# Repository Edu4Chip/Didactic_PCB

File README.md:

# Didactic PCB
This repository includes design files and documentation for Didactic PCBs and software for the power management microcontroller on the PCB.

## Folders
Doc: All documentation is gathered within this folder.
PCBs: KiCad projects Didactic main and wire bond PCBs.
PM_MCU_software: STM32CubeIDE project for the power management microcontroller on the PCB.

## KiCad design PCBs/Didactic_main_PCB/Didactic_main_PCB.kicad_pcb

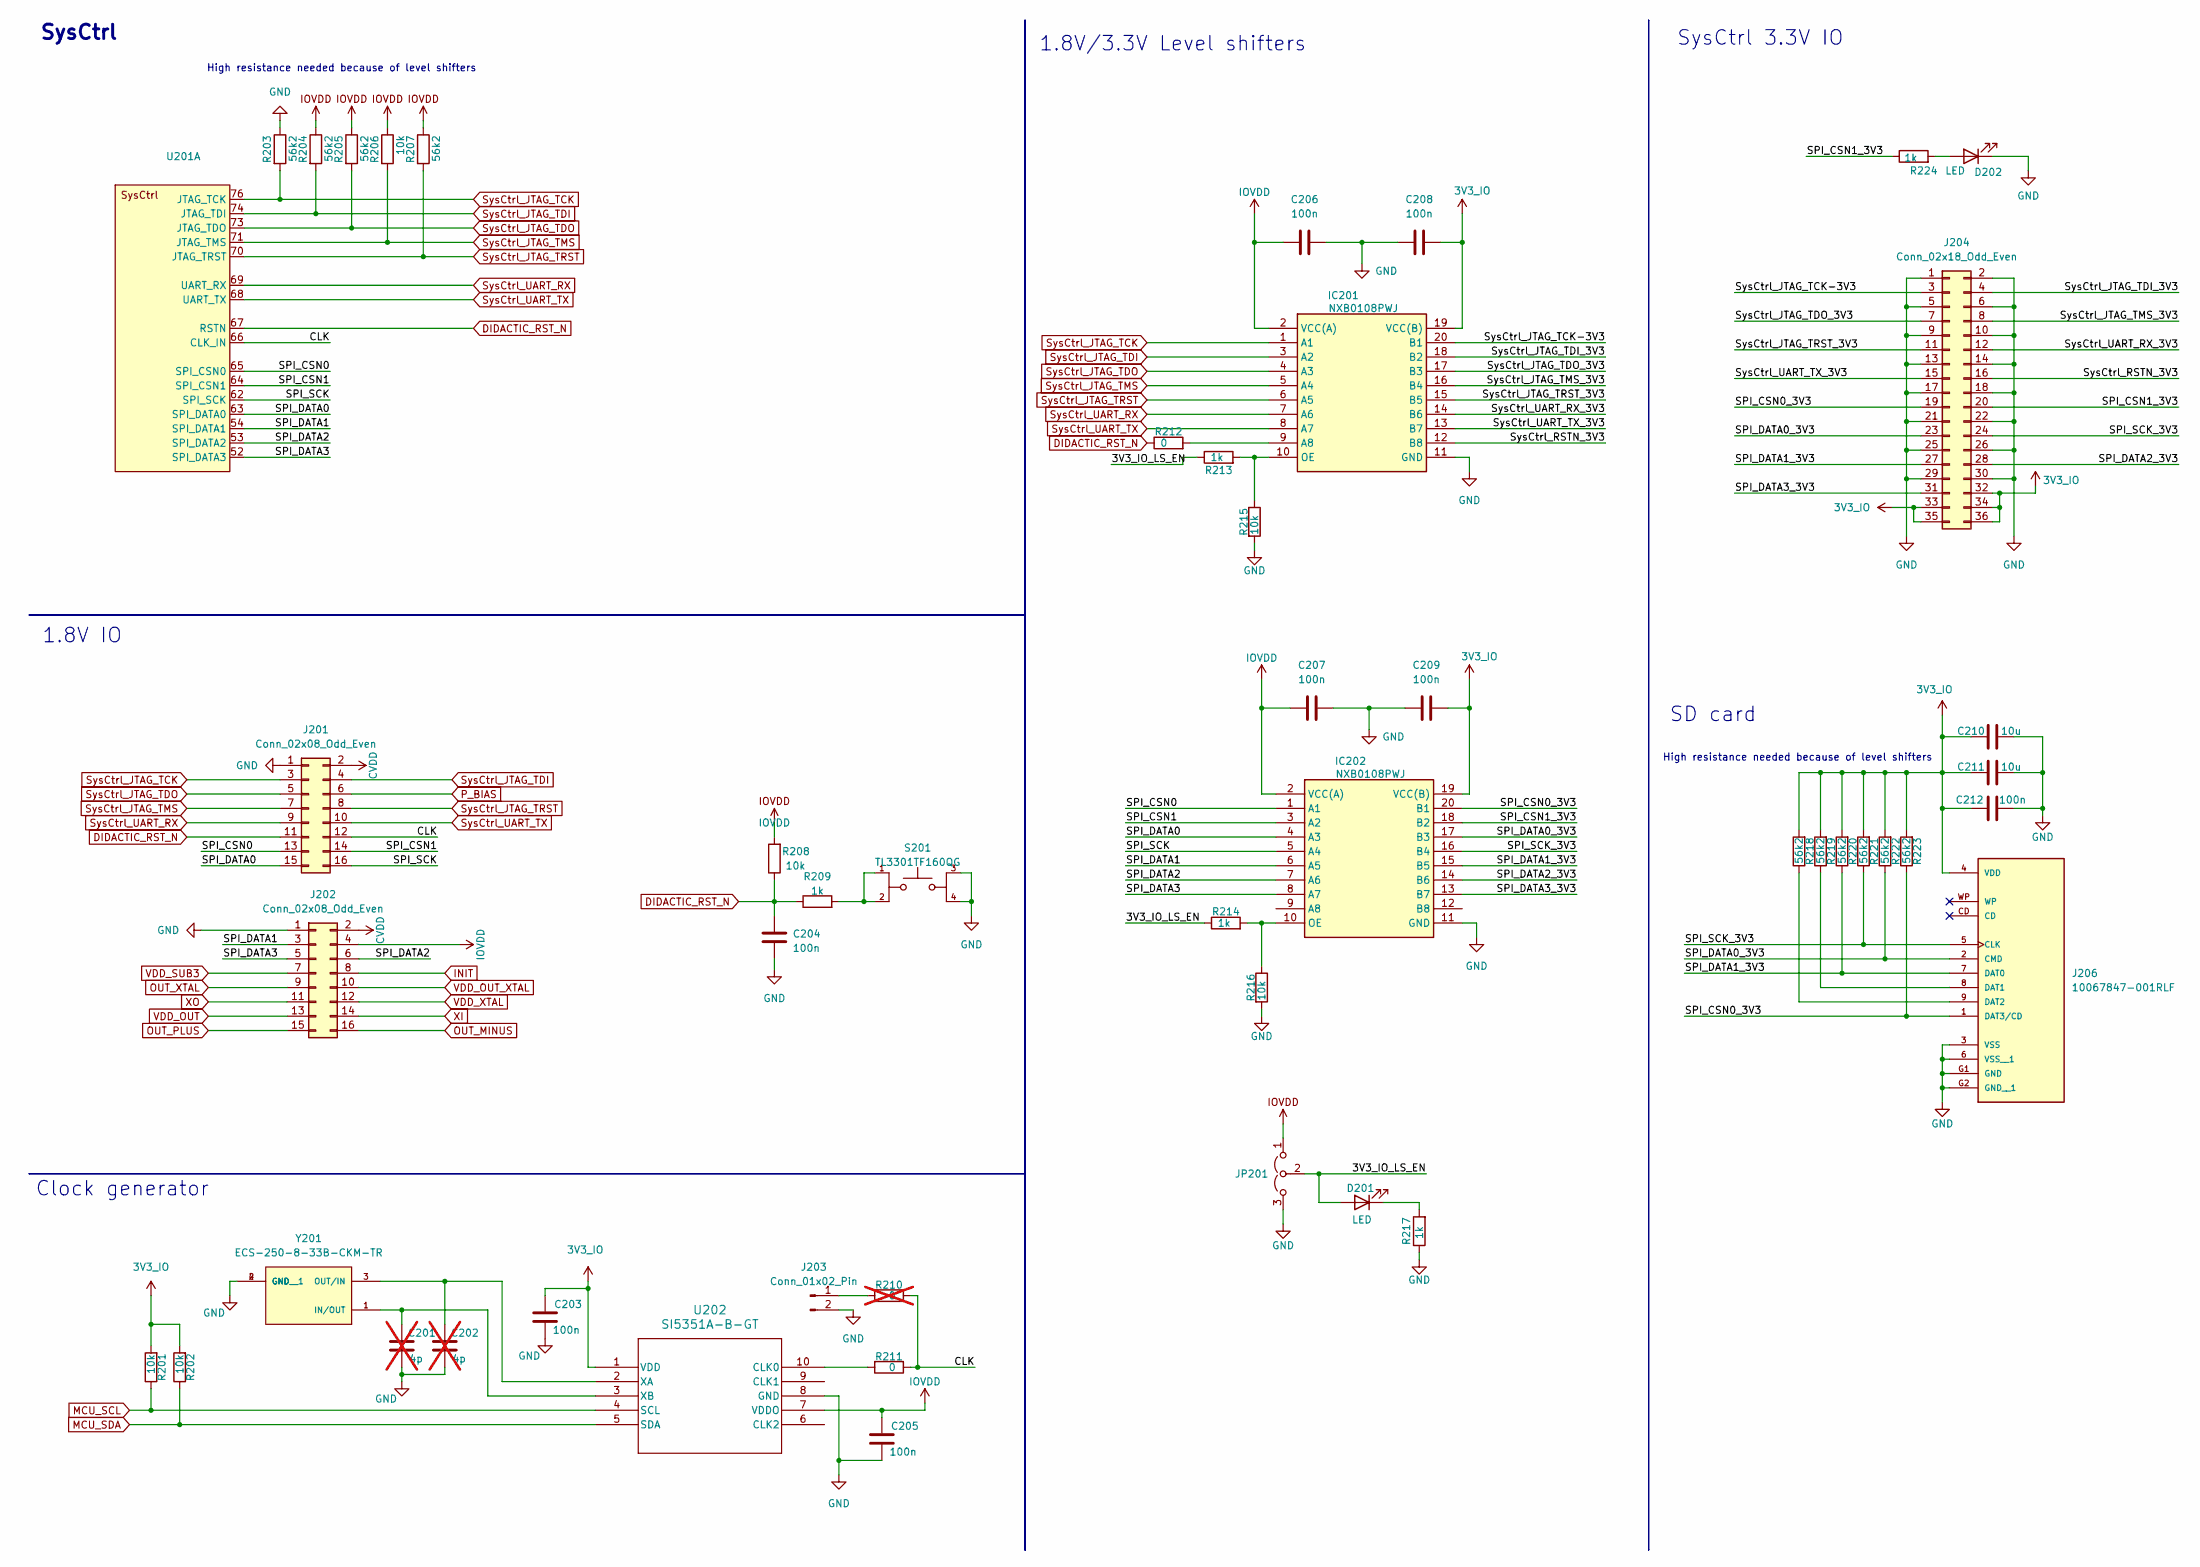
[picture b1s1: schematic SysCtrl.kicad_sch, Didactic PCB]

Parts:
C201, C202: 4p; C_0603_1608Metric; not fitted
C203, C204, C205, C206, C207, C208, C209, C212: 100n; C_0603_1608Metric; MANUFACTURER_PART_NUMBER GPC0603104
C210, C211: 10u; C_0805_2012Metric; MANUFACTURER_PART_NUMBER GPC0805106-25
D201, D202: LED; LED_0603_1608Metric; MANUFACTURER_PART_NUMBER APHD1608LSURCK
IC201, IC202: NXB0108PWJ; Mouser Part Number 771-NXB0108PWJ
J201, J202: Conn_02x08_Odd_Even; PinHeader_2x08_P2.54mm_Vertical; MANUFACTURER_PART_NUMBER 77313-101-16LF
J203: Conn_01x02_Pin; PinHeader_1x02_P2.54mm_Vertical; MANUFACTURER_PART_NUMBER 61300211121
J204: Conn_02x18_Odd_Even; PinHeader_2x18_P2.54mm_Vertical; MOUSER_PART_NUMBER 77313-101-36LF
J206: 10067847-001RLF; AMPHENOL_10067847-001RLF; PARTREV K
JP201: Jumper_3_Open; PinHeader_1x03_P2.54mm_Vertical; MANUFACTURER_PART_NUMBER 61300311121
R201, R202, R206, R208, R215, R216: 10k; R_0603_1608Metric; MANUFACTURER_PART_NUMBER GPR060310K
R203, R204, R205, R207, R218, R219, R220, R221, R222, R223: 56k2; R_0603_1608Metric; MANUFACTURER_PART_NUMBER CPF0603F56K2C1
R209, R213, R214, R217, R224: 1k; R_0603_1608Metric; MANUFACTURER_PART_NUMBER GPR06031K
R210: 0; R_0603_1608Metric; MANUFACTURER_PART_NUMBER GPR06030R; not fitted
R211, R212: 0; R_0603_1608Metric; MANUFACTURER_PART_NUMBER GPR06030R
S201: TL3301TF160QG; SW_TL3301TF160QG; PARTREV E
U201: Didactic_QFN-80_EP_12x12_Pitch0.5mm
U202: SI5351A-B-GT; MSOP10_SI5351_3X3-0P5_SKY; MANUFACTURER_PART_NUMBER SI5351A-B-GT
Y201: ECS-250-8-33B-CKM-TR; XTAL_ECS-250-8-33B-CKM-TR; MANUFACTURER_PART_NUMBER ECS-250-8-33B-CKM-TR

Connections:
3V3_IO: C203.2, C208.2, C209.2, C210.1, C211.1, C212.1, IC201.19 (VCC(B)), IC202.19 (VCC(B)), J204.32, J204.33, J204.34, J204.35, J204.36, J206.4 (VDD), R201.2, R202.2, R218.2, R219.2, R220.2, R221.2, R222.2, R223.2, U202.1 (VDD); also elsewhere on the board
/SysCtrl/3V3_IO_LS_EN: D201.2 (A), JP201.2 (C), R213.1, R214.1
/SysCtrl/CLK: J201.12, R210.1, R211.1, U201.66 (CLK_IN)
/SysCtrl/SPI_CSN0: IC202.1 (A1), J201.13, U201.65 (SPI_CSN0)
/SysCtrl/SPI_CSN0_3V3: IC202.20 (B1), J204.19, J206.1 (DAT3/CD), R223.1
/SysCtrl/SPI_CSN1: IC202.3 (A2), J201.14, U201.64 (SPI_CSN1)
/SysCtrl/SPI_CSN1_3V3: IC202.18 (B2), J204.20, R224.1
/SysCtrl/SPI_DATA0: IC202.4 (A3), J201.15, U201.63 (SPI_DATA0)
/SysCtrl/SPI_DATA0_3V3: IC202.17 (B3), J204.23, J206.2 (CMD), R222.1
/SysCtrl/SPI_DATA1: IC202.6 (A5), J202.3, U201.54 (SPI_DATA1)
/SysCtrl/SPI_DATA1_3V3: IC202.15 (B5), J204.27, J206.7 (DAT0), R220.1
/SysCtrl/SPI_DATA2: IC202.7 (A6), J202.6, U201.53 (SPI_DATA2)
/SysCtrl/SPI_DATA2_3V3: IC202.14 (B6), J204.28
/SysCtrl/SPI_DATA3: IC202.8 (A7), J202.5, U201.52 (SPI_DATA3)
/SysCtrl/SPI_DATA3_3V3: IC202.13 (B7), J204.31
/SysCtrl/SPI_SCK: IC202.5 (A4), J201.16, U201.62 (SPI_SCK)
/SysCtrl/SPI_SCK_3V3: IC202.16 (B4), J204.24, J206.5 (CLK), R221.1
/SysCtrl/SysCtrl_JTAG_TCK-3V3: IC201.20 (B1), J204.3
/SysCtrl/SysCtrl_JTAG_TDI_3V3: IC201.18 (B2), J204.4
/SysCtrl/SysCtrl_JTAG_TDO_3V3: IC201.17 (B3), J204.7
/SysCtrl/SysCtrl_JTAG_TMS_3V3: IC201.16 (B4), J204.8
/SysCtrl/SysCtrl_JTAG_TRST_3V3: IC201.15 (B5), J204.11
/SysCtrl/SysCtrl_RSTN_3V3: IC201.12 (B8), J204.16
/SysCtrl/SysCtrl_UART_RX_3V3: IC201.14 (B6), J204.12
/SysCtrl/SysCtrl_UART_TX_3V3: IC201.13 (B7), J204.15
CVDD: J201.2, J202.2; also elsewhere on the board
DIDACTIC_RST_N: C204.1, J201.11, R208.1, R209.1, R212.1, U201.67 (RSTN); also elsewhere on the board
GND: C201.1, C202.1, C203.1, C204.2, C205.1, C206.2, C207.2, C208.1, C209.1, C210.2, C211.2, C212.2, D202.1 (K), IC201.11 (GND), IC202.11 (GND), J201.1, J202.1, J203.2, J204.1, J204.2, J204.5, J204.6, J204.9, J204.10, J204.13, J204.14, J204.17, J204.18, J204.21, J204.22, J204.25, J204.26, J204.29, J204.30, J206.3 (VSS), J206.6 (VSS__1), J206.G1 (GND), J206.G2 (GND__1), JP201.3 (B), R203.1, R215.2, R216.2, R217.1, S201.3, S201.4, U202.8 (GND), Y201.2 (GND), Y201.4 (GND__1); also elsewhere on the board
INIT: J202.8; also elsewhere on the board
IOVDD: C205.2, C206.1, C207.1, IC201.2 (VCC(A)), IC202.2 (VCC(A)), J202.4, JP201.1 (A), R204.1, R205.1, R206.1, R207.1, R208.2, U202.7 (VDDO); also elsewhere on the board
MCU_SCL: R201.1, U202.4 (SCL); also elsewhere on the board
MCU_SDA: R202.1, U202.5 (SDA); also elsewhere on the board
unnamed: D201.1 (K), R217.2
unnamed: D202.2 (A), R224.2
unnamed: IC201.9 (A8), R212.2
unnamed: IC201.10 (OE), R213.2, R215.1
unnamed: IC202.10 (OE), R214.2, R216.1
unnamed: J203.1, R210.2
unnamed: J206.8 (DAT1), R219.1
unnamed: J206.9 (DAT2), R218.1
unnamed: R209.2, S201.1, S201.2
unnamed: R211.2, U202.10 (CLK0)
unnamed: C202.2, U202.2 (XA), Y201.3 (OUT/IN)
unnamed: C201.2, U202.3 (XB), Y201.1 (IN/OUT)
OUT_MINUS: J202.16; also elsewhere on the board
OUT_PLUS: J202.15; also elsewhere on the board
OUT_XTAL: J202.9; also elsewhere on the board
P_BIAS: J201.6; also elsewhere on the board
SysCtrl_JTAG_TCK: IC201.1 (A1), J201.3, R203.2, U201.76 (JTAG_TCK); also elsewhere on the board
SysCtrl_JTAG_TDI: IC201.3 (A2), J201.4, R204.2, U201.74 (JTAG_TDI); also elsewhere on the board
SysCtrl_JTAG_TDO: IC201.4 (A3), J201.5, R205.2, U201.73 (JTAG_TDO); also elsewhere on the board
SysCtrl_JTAG_TMS: IC201.5 (A4), J201.7, R206.2, U201.71 (JTAG_TMS); also elsewhere on the board
SysCtrl_JTAG_TRST: IC201.6 (A5), J201.8, R207.2, U201.70 (JTAG_TRST)
SysCtrl_UART_RX: IC201.7 (A6), J201.9, U201.69 (UART_RX); also elsewhere on the board
SysCtrl_UART_TX: IC201.8 (A7), J201.10, U201.68 (UART_TX); also elsewhere on the board
VDD_OUT: J202.13; also elsewhere on the board
VDD_OUT_XTAL: J202.10; also elsewhere on the board
VDD_SUB3: J202.7; also elsewhere on the board
VDD_XTAL: J202.12; also elsewhere on the board
XI: J202.14; also elsewhere on the board
XO: J202.11; also elsewhere on the board

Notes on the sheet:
SysCtrl 3.3V IO
1.8V/3.3V Level shifters
SD card
High resistance needed because of level shifters
SysCtrl
Clock generator
1.8V IO

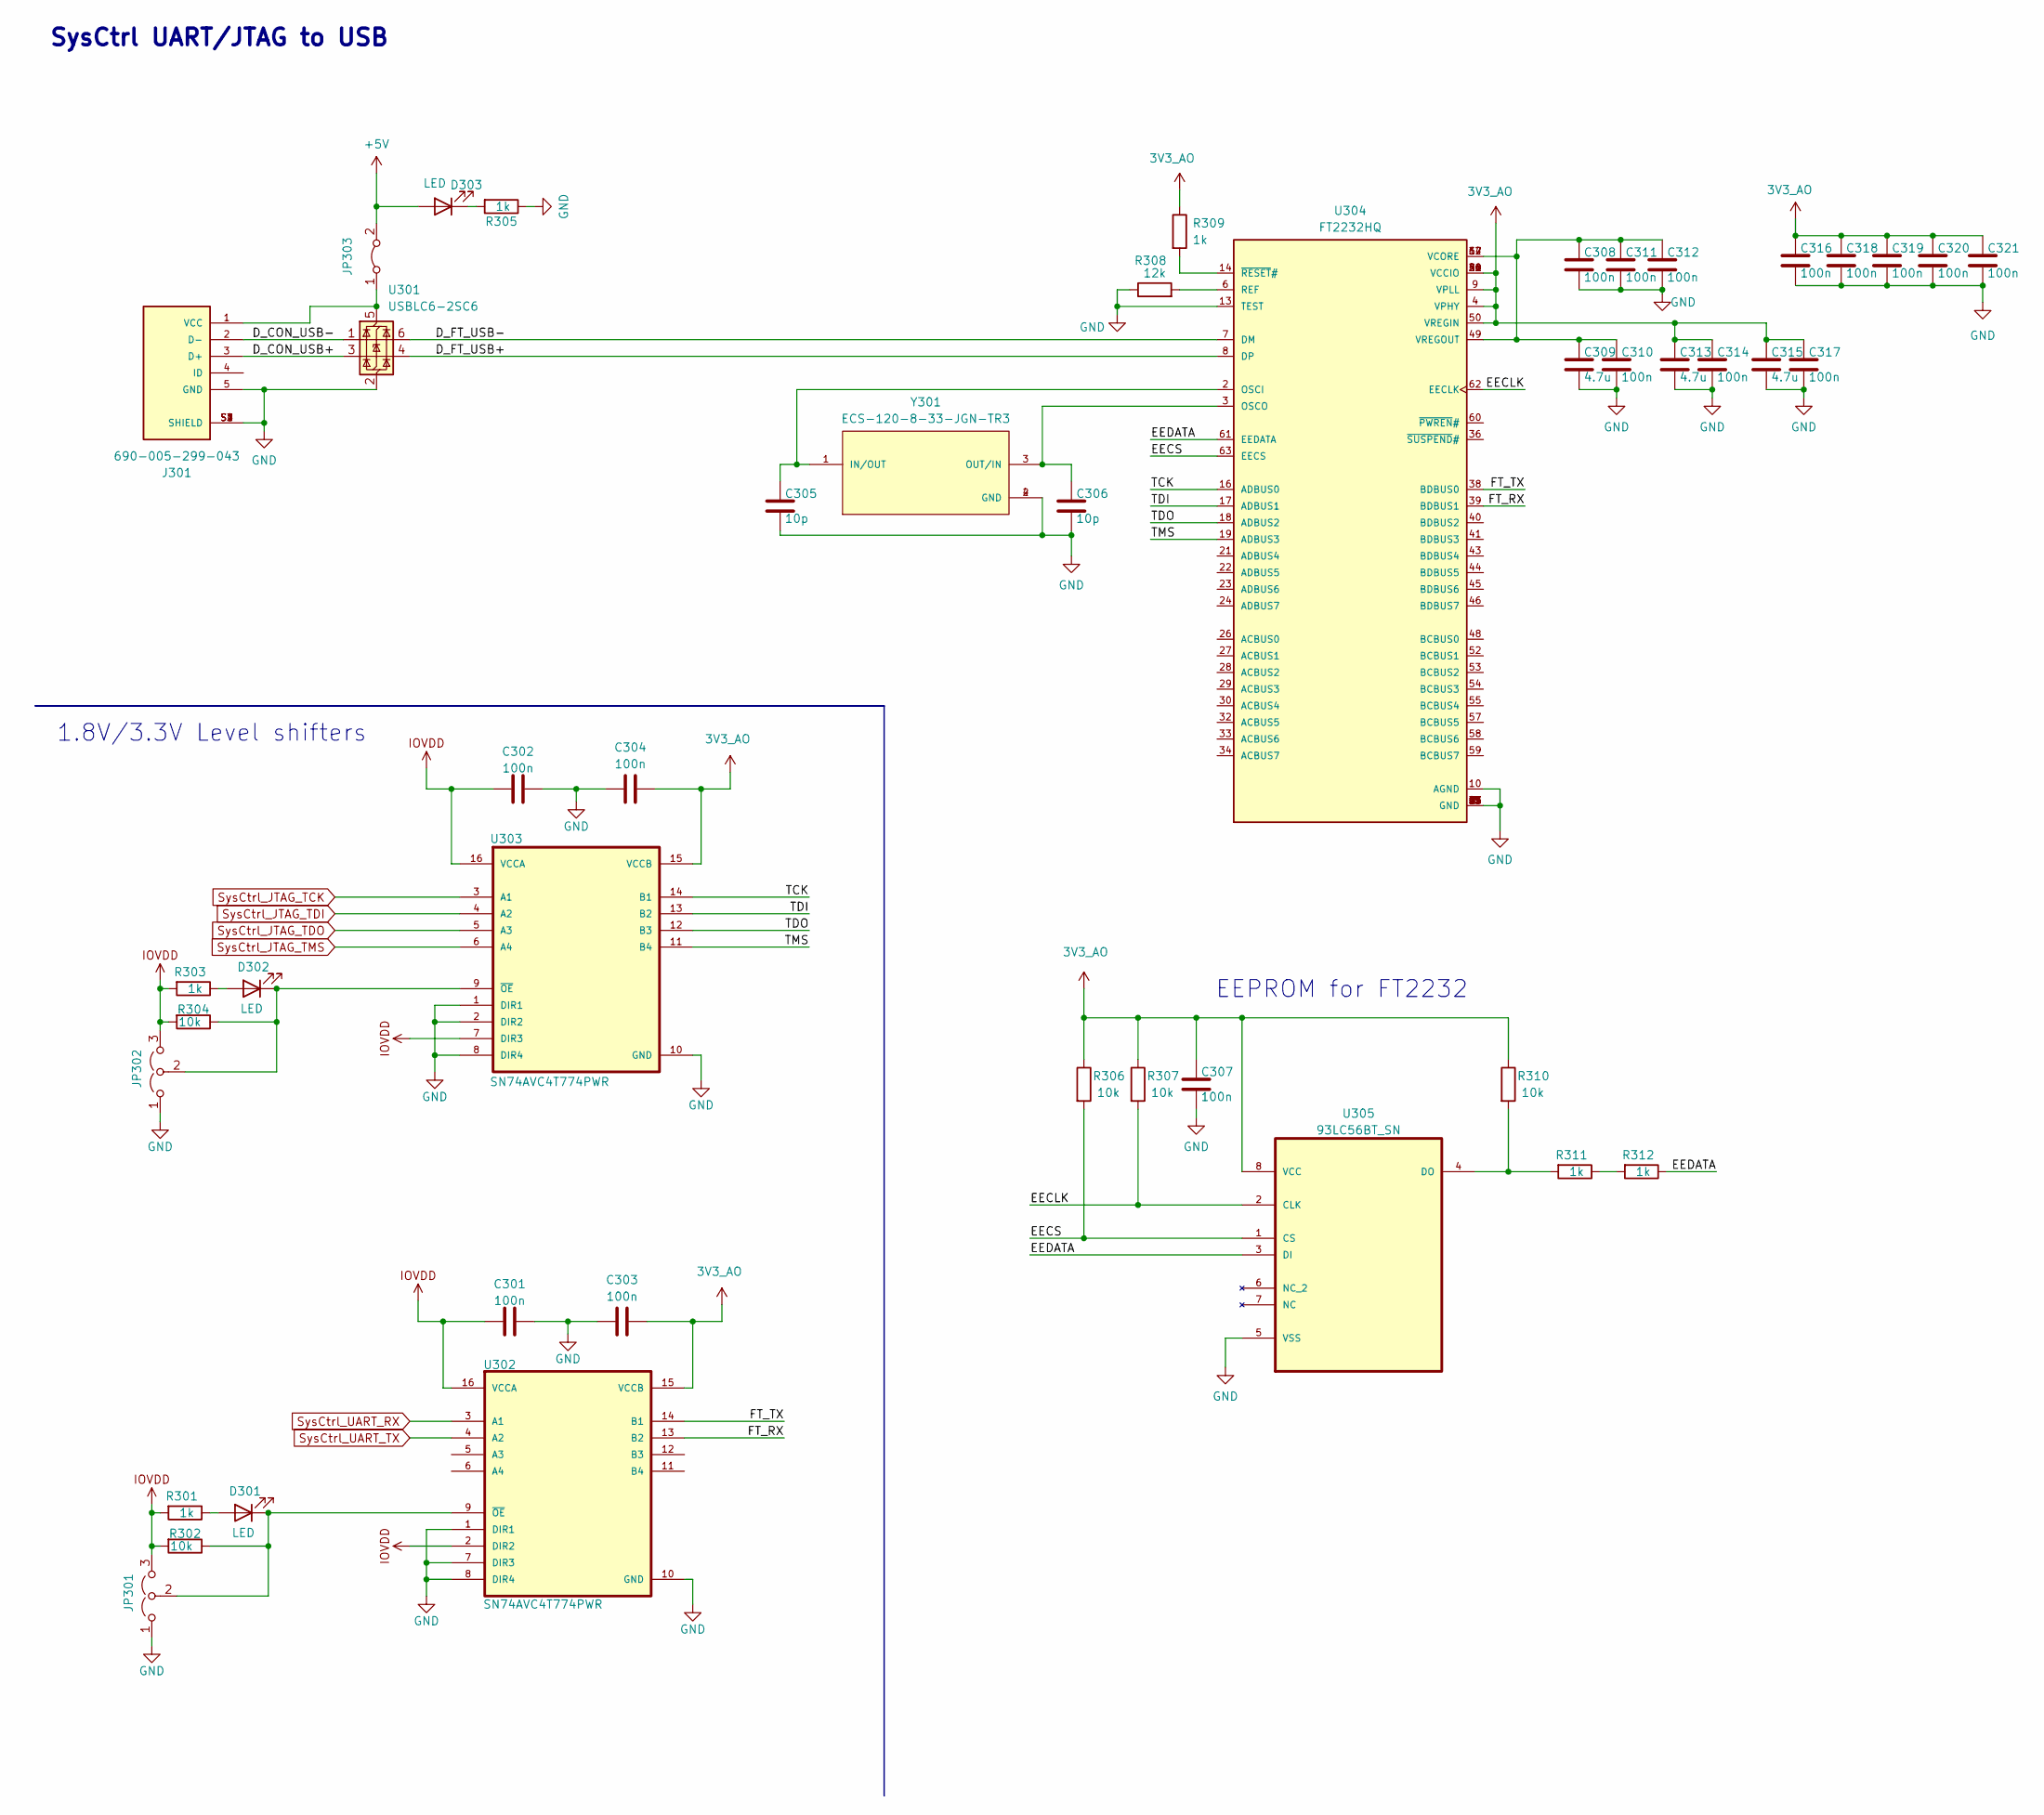
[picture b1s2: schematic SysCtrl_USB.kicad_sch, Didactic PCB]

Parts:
C301, C302, C303, C304, C307, C308, C310, C311, C312, C314, C316, C317, C318, C319, C320, C321: 100n; C_0603_1608Metric; MANUFACTURER_PART_NUMBER GPC0603104
C305, C306: 10p; C_0603_1608Metric; MANUFACTURER_PART_NUMBER GPC0603100
C309, C313, C315: 4.7u; C_0603_1608Metric; MANUFACTURER_PART_NUMBER GPC0603475-10
D301, D302, D303: LED; LED_0603_1608Metric; MANUFACTURER_PART_NUMBER APHD1608LSURCK
J301: 690-005-299-043; EDAC_690-005-299-043; PARTREV 11
JP301, JP302: Jumper_3_Open; PinHeader_1x03_P2.54mm_Vertical; MANUFACTURER_PART_NUMBER 61300311121
JP303: Jumper_2_Bridged; PinHeader_1x02_P2.54mm_Vertical; MANUFACTURER_PART_NUMBER 61300211121
R301, R303, R305, R309, R311, R312: 1k; R_0603_1608Metric; MANUFACTURER_PART_NUMBER GPR06031K
R302, R304, R306, R307, R310: 10k; R_0603_1608Metric; MANUFACTURER_PART_NUMBER GPR060310K
R308: 12k; R_0603_1608Metric; MANUFACTURER_PART_NUMBER GPR060312K
U301: USBLC6-2SC6; SOT-23-6; MANUFACTURER_PART_NUMBER USBLC6-2SC6
U302, U303: SN74AVC4T774PWR; SOP65P640X120-16N; MANUFACTURER_PART_NUMBER SN74AVC4T774PWR
U304: FT2232HQ; QFN50P900X900X100-65N; MANUFACTURER_PART_NUMBER FT2232HQ
U305: 93LC56BT_SN; SOIC127P600X175-8N; MPN 93LC56BT/SN
Y301: ECS-120-8-33-JGN-TR3; XTAL_ECS-120-8-33-JGN-TR3; MANUFACTURER_PART_NUMBER ECS-120-8-33-JGN-TR3

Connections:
3V3_AO: C303.2, C304.2, C307.1, C313.1, C314.1, C315.1, C316.1, C317.1, C318.1, C319.1, C320.1, C321.1, R306.1, R307.1, R309.1, R310.1, U302.15 (VCCB), U303.15 (VCCB), U304.4 (VPHY), U304.9 (VPLL), U304.20 (VCCIO), U304.31 (VCCIO), U304.42 (VCCIO), U304.50 (VREGIN), U304.56 (VCCIO), U305.8 (VCC); also elsewhere on the board
+5V: D303.2 (A), JP303.2 (B); also elsewhere on the board
/SysCtrl_USB/D_CON_USB+: J301.3 (D+), U301.3 (I/O2)
/SysCtrl_USB/D_CON_USB-: J301.2 (D-), U301.1 (I/O1)
/SysCtrl_USB/D_FT_USB+: U301.4 (I/O2), U304.8 (DP)
/SysCtrl_USB/D_FT_USB-: U301.6 (I/O1), U304.7 (DM)
/SysCtrl_USB/EECLK: R307.2, U304.62 (EECLK), U305.2 (CLK)
/SysCtrl_USB/EECS: R306.2, U304.63 (EECS), U305.1 (CS)
/SysCtrl_USB/EEDATA: R312.1, U304.61 (EEDATA), U305.3 (DI)
/SysCtrl_USB/FT_RX: U302.13 (B2), U304.39 (BDBUS1)
/SysCtrl_USB/FT_TX: U302.14 (B1), U304.38 (BDBUS0)
/SysCtrl_USB/TCK: U303.14 (B1), U304.16 (ADBUS0)
/SysCtrl_USB/TDI: U303.13 (B2), U304.17 (ADBUS1)
/SysCtrl_USB/TDO: U303.12 (B3), U304.18 (ADBUS2)
/SysCtrl_USB/TMS: U303.11 (B4), U304.19 (ADBUS3)
GND: C301.2, C302.2, C303.1, C304.1, C305.2, C306.2, C307.2, C308.2, C309.2, C310.2, C311.2, C312.2, C313.2, C314.2, C315.2, C316.2, C317.2, C318.2, C319.2, C320.2, C321.2, J301.5 (GND), J301.S1 (SHIELD), J301.S2 (SHIELD), J301.S3 (SHIELD), J301.S4 (SHIELD), JP301.1 (A), JP302.1 (A), R305.1, R308.1, U301.2 (GND), U302.1 (DIR1), U302.7 (DIR3), U302.8 (DIR4), U302.10 (GND), U303.1 (DIR1), U303.2 (DIR2), U303.8 (DIR4), U303.10 (GND), U304.1 (GND), U304.5 (GND), U304.10 (AGND), U304.11 (GND), U304.13 (TEST), U304.15 (GND), U304.25 (GND), U304.35 (GND), U304.47 (GND), U304.51 (GND), U304.65 (GND), U305.5 (VSS), Y301.2 (GND), Y301.4 (GND); also elsewhere on the board
IOVDD: C301.1, C302.1, JP301.3 (B), JP302.3 (B), R301.2, R302.2, R303.2, R304.2, U302.2 (DIR2), U302.16 (VCCA), U303.7 (DIR3), U303.16 (VCCA); also elsewhere on the board
unnamed: D301.2 (A), R301.1
unnamed: D301.1 (K), JP301.2 (C), R302.1, U302.9 (~OE)
unnamed: D302.2 (A), R303.1
unnamed: D302.1 (K), JP302.2 (C), R304.1, U303.9 (~OE)
unnamed: D303.1 (K), R305.2
unnamed: J301.1 (VCC), JP303.1 (A), U301.5 (VBUS)
unnamed: R311.1, R312.2
unnamed: C305.1, U304.2 (OSCI), Y301.1 (IN/OUT)
unnamed: C306.1, U304.3 (OSCO), Y301.3 (OUT/IN)
unnamed: R308.2, U304.6 (REF)
unnamed: C308.1, C309.1, C310.1, C311.1, C312.1, U304.12 (VCORE), U304.37 (VCORE), U304.49 (VREGOUT), U304.64 (VCORE)
unnamed: R309.2, U304.14 (~RESET#)
unnamed: R310.2, R311.2, U305.4 (DO)
SysCtrl_JTAG_TCK: U303.3 (A1); also elsewhere on the board
SysCtrl_JTAG_TDI: U303.4 (A2); also elsewhere on the board
SysCtrl_JTAG_TDO: U303.5 (A3); also elsewhere on the board
SysCtrl_JTAG_TMS: U303.6 (A4); also elsewhere on the board
SysCtrl_UART_RX: U302.3 (A1); also elsewhere on the board
SysCtrl_UART_TX: U302.4 (A2); also elsewhere on the board

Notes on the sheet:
SysCtrl UART/JTAG to USB
1.8V/3.3V Level shifters
EEPROM for FT2232

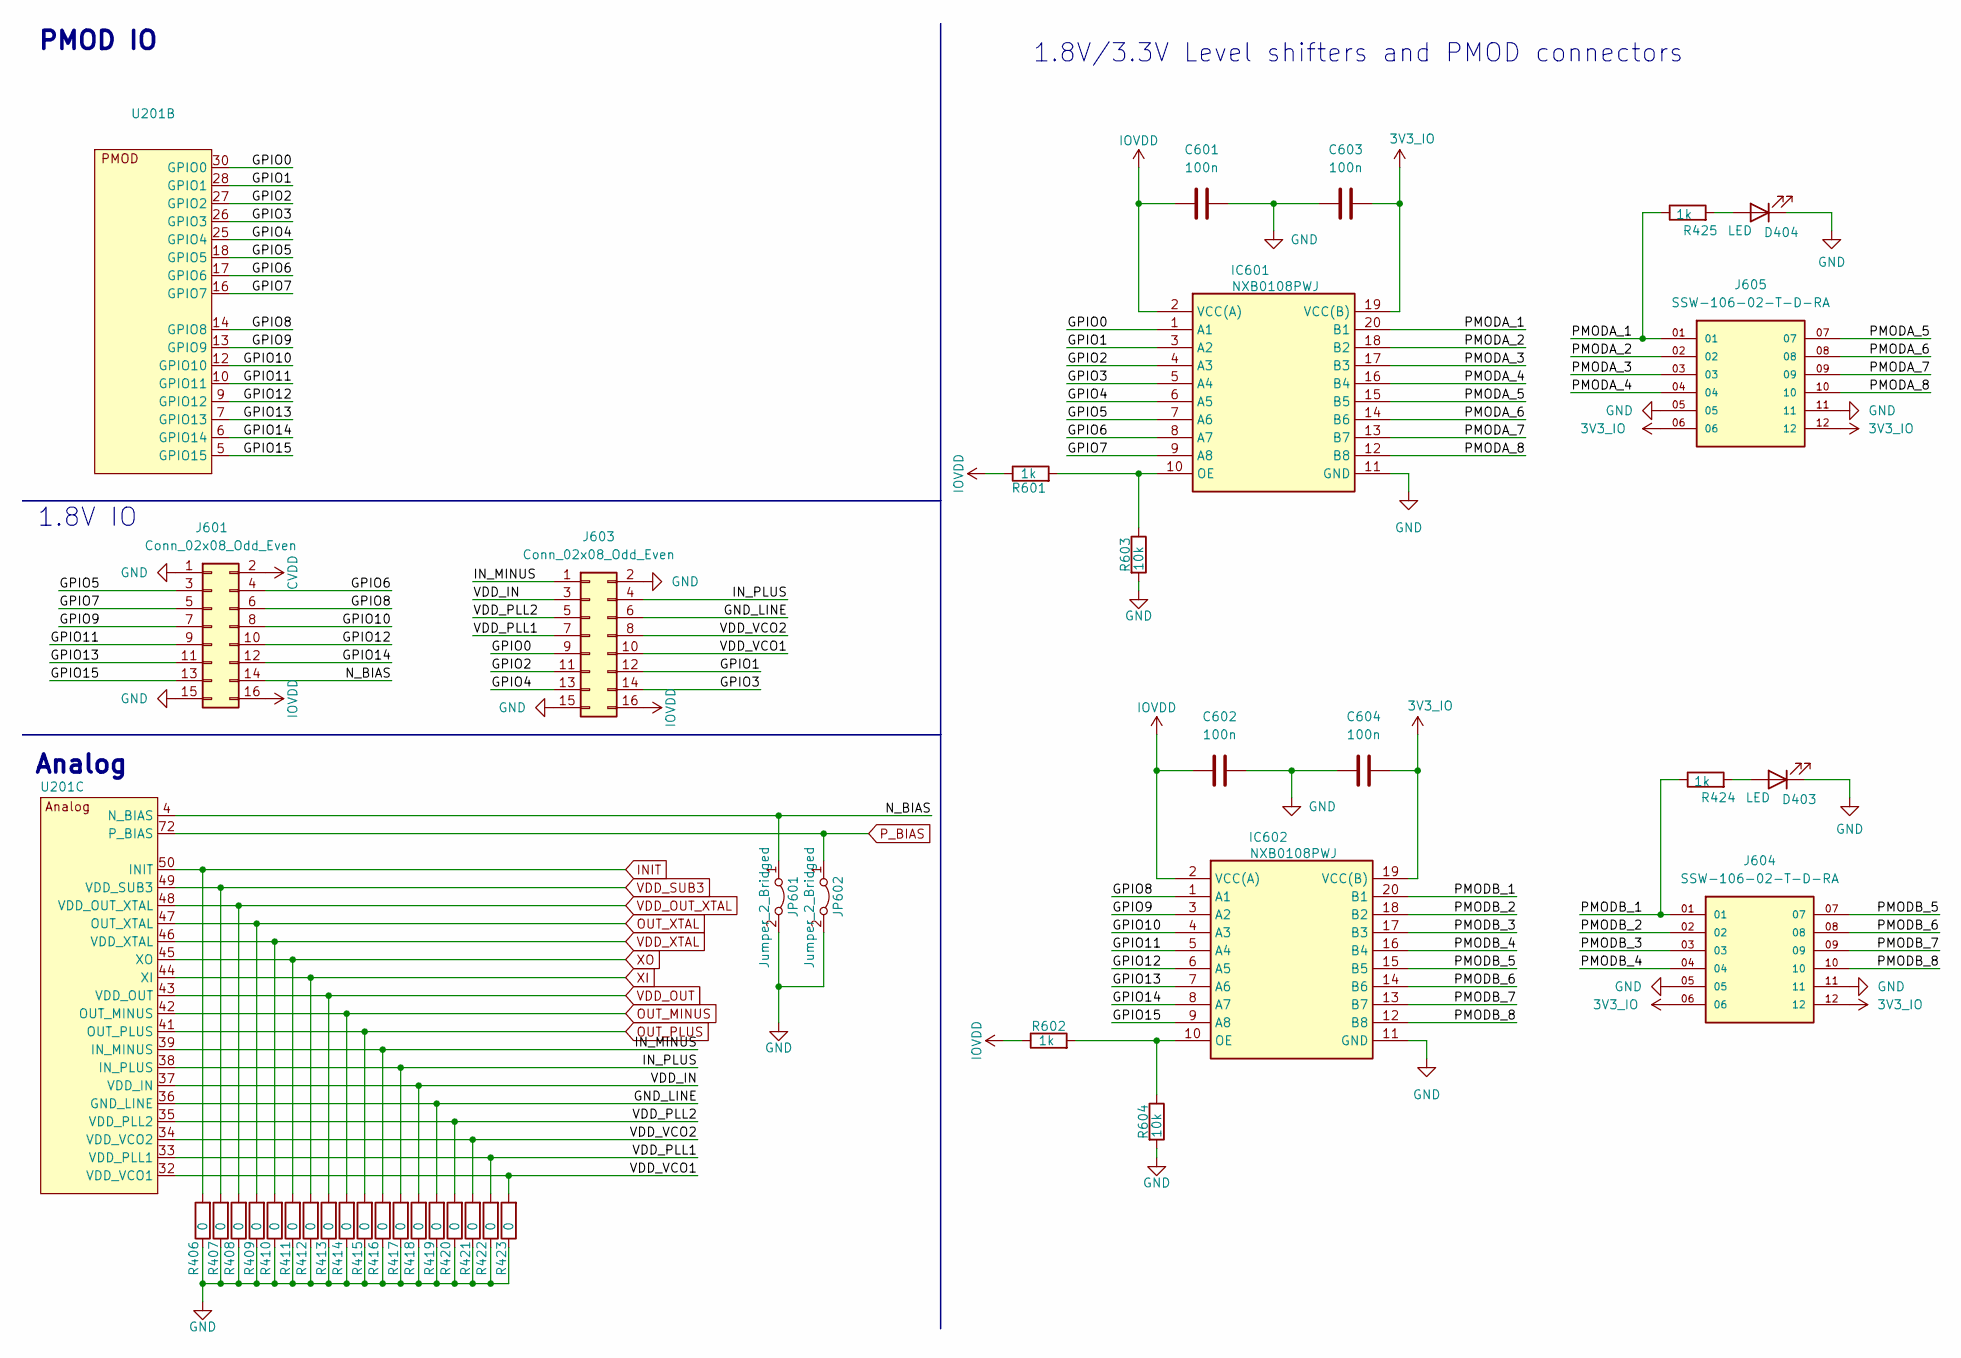
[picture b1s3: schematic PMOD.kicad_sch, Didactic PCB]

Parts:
C601, C602, C603, C604: 100n; C_0603_1608Metric; MANUFACTURER_PART_NUMBER GPC0603104
D403, D404: LED; LED_0603_1608Metric; MANUFACTURER_PART_NUMBER APHD1608LSURCK
IC601, IC602: NXB0108PWJ; Mouser Part Number 771-NXB0108PWJ
J601, J603: Conn_02x08_Odd_Even; PinHeader_2x08_P2.54mm_Vertical; MANUFACTURER_PART_NUMBER 77313-101-16LF
J604, J605: SSW-106-02-T-D-RA; SAMTEC_SSW-106-02-T-D-RA; PARTREV R
JP601, JP602: Jumper_2_Bridged; PinHeader_1x02_P2.54mm_Vertical; MANUFACTURER_PART_NUMBER 61300211121
R406, R407, R408, R409, R410, R411, R412, R413, R414, R415, R416, R417, R418, R419, R420, R421, R422, R423: 0; R_0603_1608Metric; MANUFACTURER_PART_NUMBER GPR06030R
R424, R425, R601, R602: 1k; R_0603_1608Metric; MANUFACTURER_PART_NUMBER GPR06031K
R603, R604: 10k; R_0603_1608Metric; MANUFACTURER_PART_NUMBER GPR060310K
U201: Didactic_QFN-80_EP_12x12_Pitch0.5mm

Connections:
3V3_IO: C603.2, C604.2, IC601.19 (VCC(B)), IC602.19 (VCC(B)), J604.06, J604.12, J605.06, J605.12; also elsewhere on the board
/PMOD/GND_LINE: J603.6, R419.2, U201.36 (GND_LINE)
/PMOD/GPIO0: IC601.1 (A1), J603.9, U201.30 (GPIO0)
/PMOD/GPIO1: IC601.3 (A2), J603.12, U201.28 (GPIO1)
/PMOD/GPIO2: IC601.4 (A3), J603.11, U201.27 (GPIO2)
/PMOD/GPIO3: IC601.5 (A4), J603.14, U201.26 (GPIO3)
/PMOD/GPIO4: IC601.6 (A5), J603.13, U201.25 (GPIO4)
/PMOD/GPIO5: IC601.7 (A6), J601.3, U201.18 (GPIO5)
/PMOD/GPIO6: IC601.8 (A7), J601.4, U201.17 (GPIO6)
/PMOD/GPIO7: IC601.9 (A8), J601.5, U201.16 (GPIO7)
/PMOD/GPIO8: IC602.1 (A1), J601.6, U201.14 (GPIO8)
/PMOD/GPIO9: IC602.3 (A2), J601.7, U201.13 (GPIO9)
/PMOD/GPIO10: IC602.4 (A3), J601.8, U201.12 (GPIO10)
/PMOD/GPIO11: IC602.5 (A4), J601.9, U201.10 (GPIO11)
/PMOD/GPIO12: IC602.6 (A5), J601.10, U201.9 (GPIO12)
/PMOD/GPIO13: IC602.7 (A6), J601.11, U201.7 (GPIO13)
/PMOD/GPIO14: IC602.8 (A7), J601.12, U201.6 (GPIO14)
/PMOD/GPIO15: IC602.9 (A8), J601.13, U201.5 (GPIO15)
/PMOD/IN_MINUS: J603.1, R416.2, U201.39 (IN_MINUS)
/PMOD/IN_PLUS: J603.4, R417.2, U201.38 (IN_PLUS)
/PMOD/N_BIAS: J601.14, JP601.1 (A), U201.4 (N_BIAS)
/PMOD/PMODA_1: IC601.20 (B1), J605.01, R425.1
/PMOD/PMODA_2: IC601.18 (B2), J605.02
/PMOD/PMODA_3: IC601.17 (B3), J605.03
/PMOD/PMODA_4: IC601.16 (B4), J605.04
/PMOD/PMODA_5: IC601.15 (B5), J605.07
/PMOD/PMODA_6: IC601.14 (B6), J605.08
/PMOD/PMODA_7: IC601.13 (B7), J605.09
/PMOD/PMODA_8: IC601.12 (B8), J605.10
/PMOD/PMODB_1: IC602.20 (B1), J604.01, R424.1
/PMOD/PMODB_2: IC602.18 (B2), J604.02
/PMOD/PMODB_3: IC602.17 (B3), J604.03
/PMOD/PMODB_4: IC602.16 (B4), J604.04
/PMOD/PMODB_5: IC602.15 (B5), J604.07
/PMOD/PMODB_6: IC602.14 (B6), J604.08
/PMOD/PMODB_7: IC602.13 (B7), J604.09
/PMOD/PMODB_8: IC602.12 (B8), J604.10
/PMOD/VDD_IN: J603.3, R418.2, U201.37 (VDD_IN)
/PMOD/VDD_PLL1: J603.7, R422.2, U201.33 (VDD_PLL1)
/PMOD/VDD_PLL2: J603.5, R420.2, U201.35 (VDD_PLL2)
/PMOD/VDD_VCO1: J603.10, R423.2, U201.32 (VDD_VCO1)
/PMOD/VDD_VCO2: J603.8, R421.2, U201.34 (VDD_VCO2)
CVDD: J601.2; also elsewhere on the board
GND: C601.2, C602.2, C603.1, C604.1, D403.1 (K), D404.1 (K), IC601.11 (GND), IC602.11 (GND), J601.1, J601.15, J603.2, J603.15, J604.05, J604.11, J605.05, J605.11, JP601.2 (B), JP602.2 (B), R406.1, R407.1, R408.1, R409.1, R410.1, R411.1, R412.1, R413.1, R414.1, R415.1, R416.1, R417.1, R418.1, R419.1, R420.1, R421.1, R422.1, R423.1, R603.2, R604.2; also elsewhere on the board
INIT: R406.2, U201.50 (INIT); also elsewhere on the board
IOVDD: C601.1, C602.1, IC601.2 (VCC(A)), IC602.2 (VCC(A)), J601.16, J603.16, R601.1, R602.1; also elsewhere on the board
unnamed: D403.2 (A), R424.2
unnamed: D404.2 (A), R425.2
unnamed: IC601.10 (OE), R601.2, R603.1
unnamed: IC602.10 (OE), R602.2, R604.1
OUT_MINUS: R414.2, U201.42 (OUT_MINUS); also elsewhere on the board
OUT_PLUS: R415.2, U201.41 (OUT_PLUS); also elsewhere on the board
OUT_XTAL: R409.2, U201.47 (OUT_XTAL); also elsewhere on the board
P_BIAS: JP602.1 (A), U201.72 (P_BIAS); also elsewhere on the board
VDD_OUT: R413.2, U201.43 (VDD_OUT); also elsewhere on the board
VDD_OUT_XTAL: R408.2, U201.48 (VDD_OUT_XTAL); also elsewhere on the board
VDD_SUB3: R407.2, U201.49 (VDD_SUB3); also elsewhere on the board
VDD_XTAL: R410.2, U201.46 (VDD_XTAL); also elsewhere on the board
XI: R412.2, U201.44 (XI); also elsewhere on the board
XO: R411.2, U201.45 (XO); also elsewhere on the board

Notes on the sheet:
PMOD IO
Analog
1.8V IO
1.8V/3.3V Level shifters and PMOD connectors

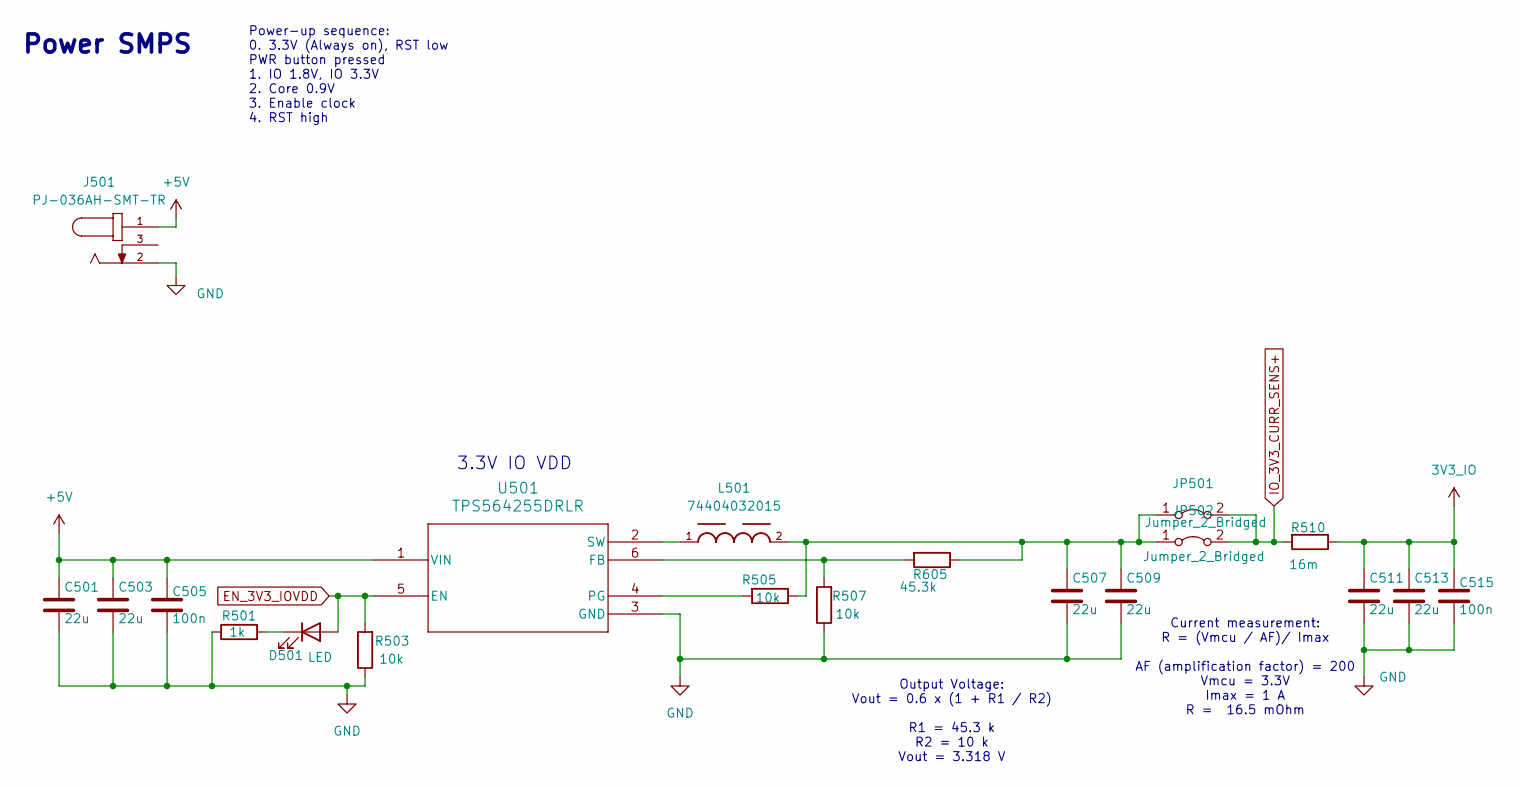
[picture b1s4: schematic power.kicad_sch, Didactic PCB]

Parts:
C501, C503, C507, C509, C511, C513: 22u; C_1206_3216Metric; MANUFACTURER_PART_NUMBER CL31A226KAHNNNE
C505, C515: 100n; C_0603_1608Metric; MANUFACTURER_PART_NUMBER GPC0603104
D501: LED; LED_0603_1608Metric; MANUFACTURER_PART_NUMBER APHD1608LSURCK
J501: PJ-036AH-SMT-TR; CUI_PJ-036AH-SMT-TR; MANUFACTURER_PART_NUMBER PJ-036AH-SMT-TR; DIGI-KEY_PART_NUMBER CP-036AHPJCT-ND
JP501, JP502: Jumper_2_Bridged; PinHeader_1x02_P2.54mm_Vertical; MANUFACTURER_PART_NUMBER 61300211121
L501: 74404032015; WE-LQS_3015; MANUFACTURER_PART_NUMBER 74404032015
R501: 1k; R_0603_1608Metric; MANUFACTURER_PART_NUMBER GPR06031K
R503, R505, R507: 10k; R_0603_1608Metric; MANUFACTURER_PART_NUMBER GPR060310K
R510: 16m; R_1206_3216Metric; MANUFACTURER_PART_NUMBER ERJ-8CWFR016V
R605: 45.3k; R_0603_1608Metric; MANUFACTURER_PART_NUMBER CPF0603F45K3C1
U501: TPS564255DRLR; TPS564242DRLR_TEX; MANUFACTURER_PART_NUMBER TPS564255DRLR

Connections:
3V3_IO: C511.2, C513.2, C515.1, R510.1; also elsewhere on the board
+5V: C501.2, C503.2, C505.1, J501.1, U501.1 (VIN); also elsewhere on the board
EN_3V3_IOVDD: D501.2 (A), R503.2, U501.5 (EN); also elsewhere on the board
GND: C501.1, C503.1, C505.2, C507.1, C509.1, C511.1, C513.1, C515.2, J501.2, R501.1, R503.1, R507.1, U501.3 (GND); also elsewhere on the board
IO_3V3_CURR_SENS+: JP501.2 (B), JP502.2 (B), R510.2; also elsewhere on the board
unnamed: D501.1 (K), R501.2
unnamed: C507.2, C509.2, JP501.1 (A), JP502.1 (A), L501.2, R505.1, R605.1
unnamed: R507.2, R605.2, U501.6 (FB)
unnamed: R505.2, U501.4 (PG)
unnamed: L501.1, U501.2 (SW)

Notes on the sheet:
Current measurement: R = (Vmcu / AF)/ Imax AF (amplification factor) = 200 Vmcu = 3.3V Imax = 1 A R = 16.5 mOhm
Power SMPS
Output Voltage: Vout = 0.6 x (1 + R1 / R2) R1 = 45.3 k R2 = 10 k Vout = 3.318 V
Power-up sequence: 0. 3.3V (Always on), RST low PWR button pressed 1. IO 1.8V, IO 3.3V 2. Core 0.9V 3. Enable clock 4. RST high
3.3V IO VDD
